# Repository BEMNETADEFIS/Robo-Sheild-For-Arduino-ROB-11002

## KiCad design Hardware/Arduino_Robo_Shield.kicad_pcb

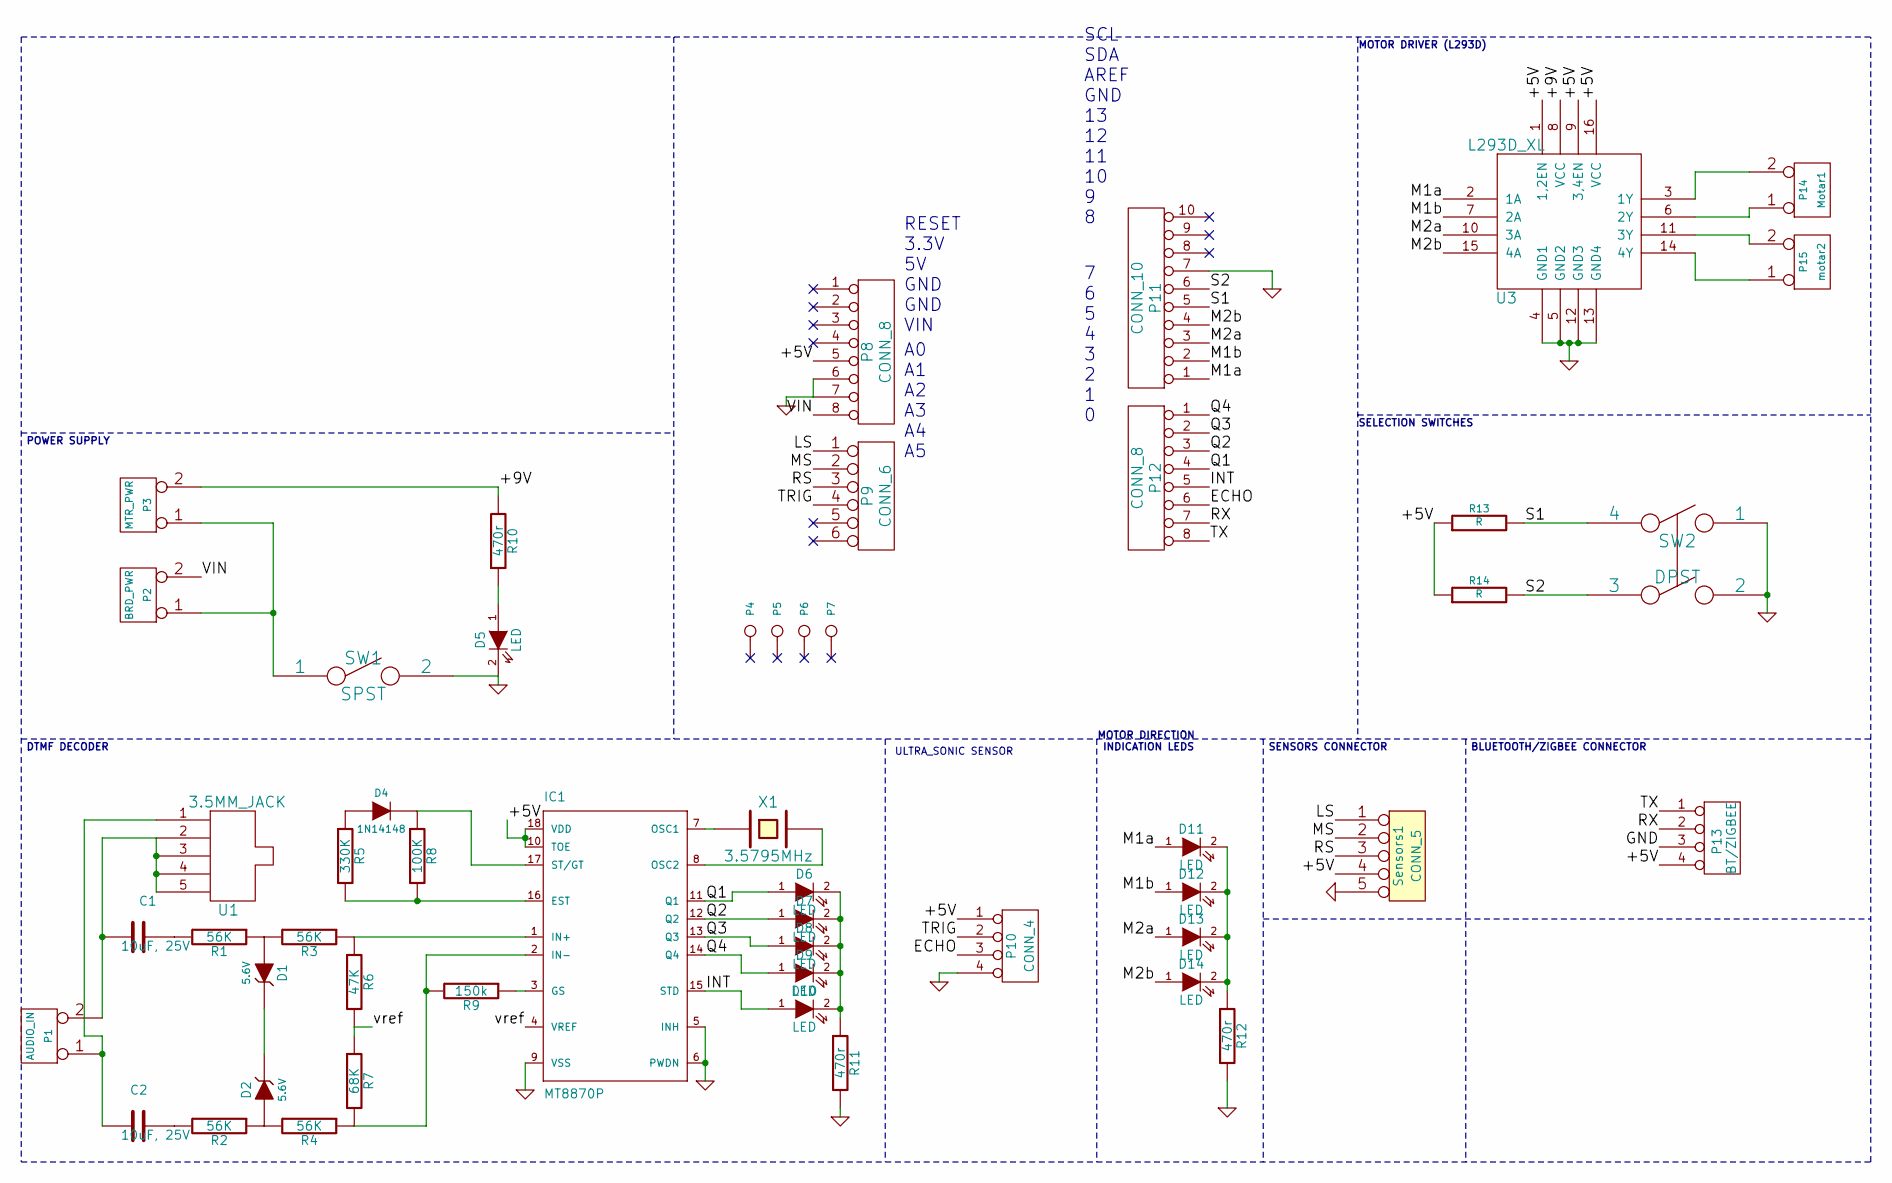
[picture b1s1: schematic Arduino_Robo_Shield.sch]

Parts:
C1, C2: 10uF, 25V
D1, D2: 5.6V
D4: 1N14148
D5, D6, D7, D8, D9, D10, D11, D12, D13, D14: LED
IC1: MT8870P; mitel-DIL18
P1: AUDIO_IN
P2: BRD_PWR
P3: MTR_PWR
P4, P5, P6, P7: CONN_1
P8, P12: CONN_8
P9: CONN_6
P10: CONN_4
P11: CONN_10
P13: BT/ZIGBEE
P14: Motar1
P15: motar2
R1, R2, R3, R4: 56K
R5: 330K
R6: 47K
R7: 68K
R8: 100K
R9: 150k
R10, R11, R12: 470r
R13, R14: R
SW1: SPST
SW2: DPST
Sensors1: CONN_5
U1: 3.5MM_JACK
U3: L293D_XL
X1: 3.5795MHz

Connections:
/+5V: IC1.10 (TOE), IC1.18 (VDD), P8.5, P10.1, P13.4, R13.1, R14.1, Sensors1.4, U3.1 (1,2EN), U3.9 (3,4EN), U3.16 (VCC)
/+9V: P3.2 (PM), R10.2, U3.8 (VCC)
/ECHO: P10.3, P12.6
/INT: D10.1 (A), IC1.15 (STD), P12.5
/LS: P9.1, Sensors1.1
/M1a: D11.1 (A), P11.1, U3.2 (1A)
/M1b: D12.1 (A), P11.2, U3.7 (2A)
/M2a: D13.1 (A), P11.3, U3.10 (3A)
/M2b: D14.1 (A), P11.4, U3.15 (4A)
/MS: P9.2, Sensors1.2
/Q1: D6.1 (A), IC1.11 (Q1), P12.4
/Q2: D7.1 (A), IC1.12 (Q2), P12.3
/Q3: D8.1 (A), IC1.13 (Q3), P12.2
/Q4: D9.1 (A), IC1.14 (Q4), P12.1
/RS: P9.3, Sensors1.3
/RX: P12.7, P13.2
/S1: P11.5, R13.2, SW2.4
/S2: P11.6, R14.2, SW2.3
/TRIG: P9.4, P10.2
/TX: P12.8, P13.1
/VIN: P2.2 (PM), P8.8
/vref: IC1.4 (VREF), R6.2, R7.1
GND: D5.2 (K), IC1.5 (INH), IC1.6 (PWDN), IC1.9 (VSS), P8.6, P8.7, P10.4, P11.7, P13.3, R11.2, R12.2, SW1.2, SW2.1, SW2.2, Sensors1.5, U3.4 (GND1), U3.5 (GND2), U3.12 (GND3), U3.13 (GND4)
unnamed: IC1.3 (GS), R9.1
unnamed: D1.2 (K), D2.2 (K)
unnamed: IC1.1 (IN+), R3.1, R6.1
unnamed: D4.2 (K), IC1.17 (ST/GT), R8.1
unnamed: IC1.7 (OSC1), X1.1
unnamed: IC1.8 (OSC2), X1.2
unnamed: P2.1, P3.1, SW1.1
unnamed: D5.1 (A), R10.1
unnamed: P15.1, U3.14 (4Y)
unnamed: P14.2 (PM), U3.3 (1Y)
unnamed: P15.2 (PM), U3.11 (3Y)
unnamed: P14.1, U3.6 (2Y)
unnamed: D2.1 (A), R2.1, R4.2
unnamed: D1.1 (A), R1.1, R3.2
unnamed: C2.2, P1.1, U1.1
unnamed: C2.1, R2.2
unnamed: C1.2, P1.2 (PM), U1.2, U1.3, U1.4, U1.5
unnamed: C1.1, R1.2
unnamed: D4.1 (A), R5.1
unnamed: IC1.16 (EST), R5.2, R8.2
unnamed: D6.2 (K), D7.2 (K), D8.2 (K), D9.2 (K), D10.2 (K), R11.1
unnamed: IC1.2 (IN-), R4.1, R7.2, R9.2
unnamed: D11.2 (K), D12.2 (K), D13.2 (K), D14.2 (K), R12.1

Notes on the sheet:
MOTOR DRIVER (L293D)
POWER SUPPLY
DTMF DECODER
MOTOR DIRECTION INDICATION LEDS
SENSORS CONNECTOR
BLUETOOTH/ZIGBEE CONNECTOR
SELECTION SWITCHES
7 6 5 4 3 2 1 0
SCL SDA AREF GND 13 12 11 10 9 8
A0 A1 A2 A3 A4 A5
RESET 3.3V 5V GND GND VIN
ULTRA_SONIC SENSOR

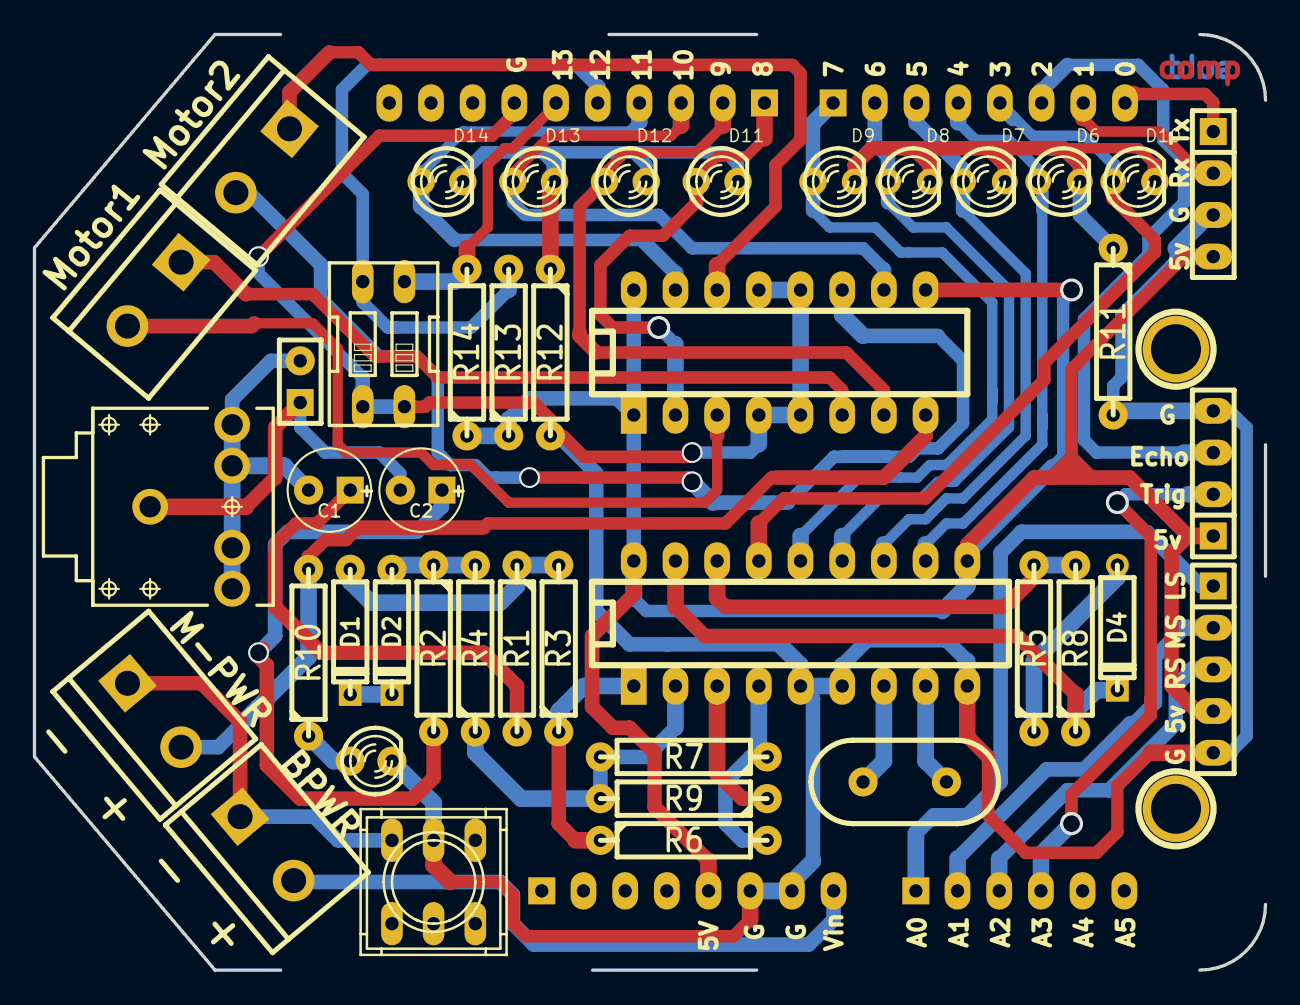
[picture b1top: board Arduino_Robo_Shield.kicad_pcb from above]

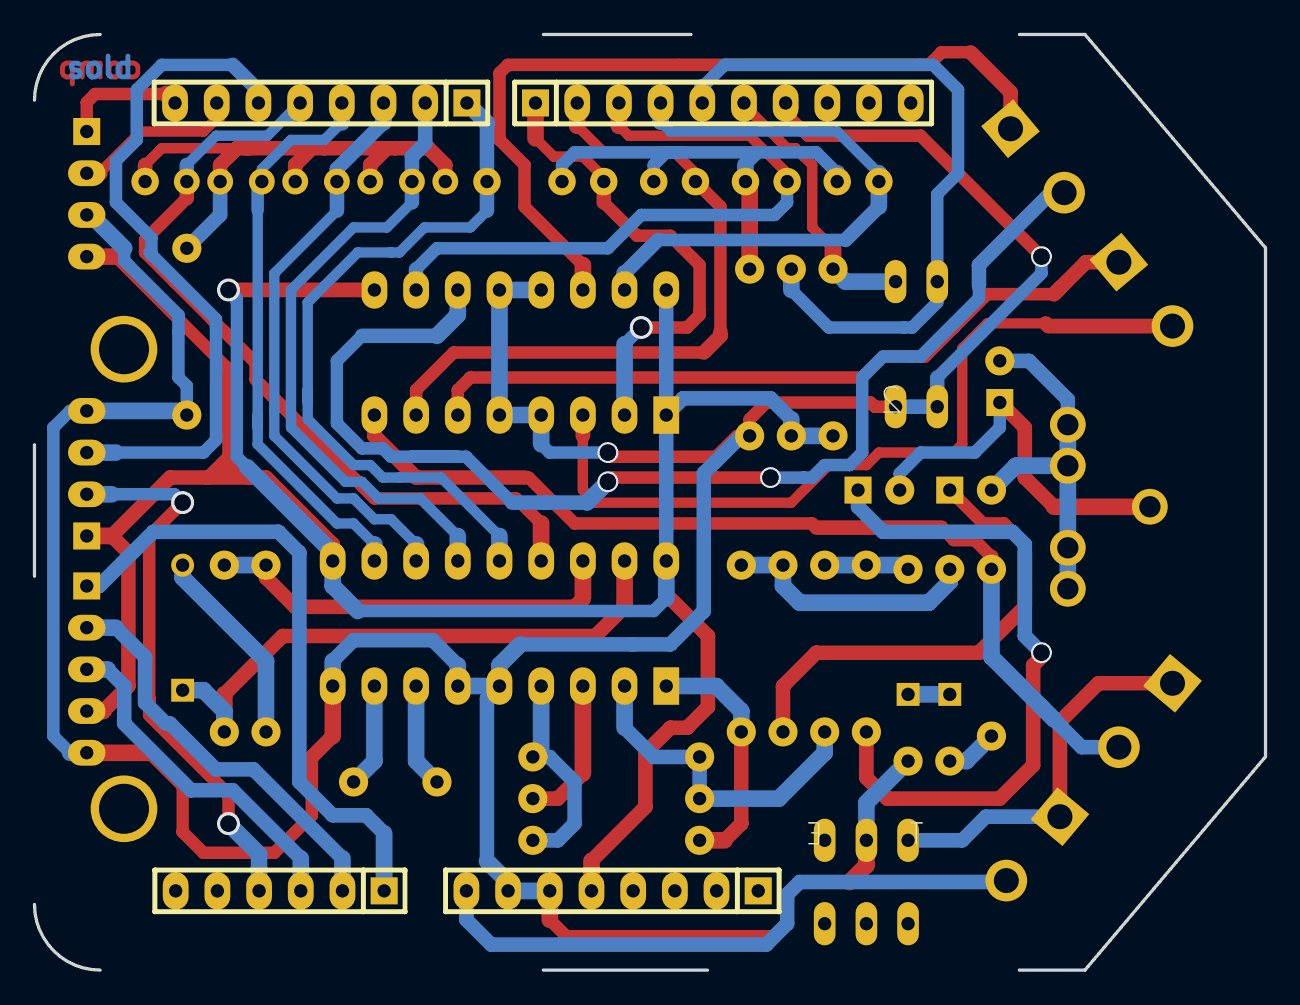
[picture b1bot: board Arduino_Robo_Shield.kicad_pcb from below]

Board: 2 copper layers, 75.0 x 57.0 mm, 49 parts (4 on the bottom side), 46 nets.

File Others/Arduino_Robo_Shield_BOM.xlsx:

Id | Designator | Package | Quantity | Designation | Supplier and ref
1 | SW1 | switch-misc-9077-2 | 1 | SPST
2 | U1 | SparkFun-AUDIO-JACK | 1 | 3.5MM_JACK
3 | P12,P8 | SIL-8 | 2 | CONN_8
4 | P9 | SIL-6 | 1 | CONN_6
5 | Sensors1 | SIL-5 | 1 | CONN_5
6 | P13 | SIL-4 | 1 | BT/ZIGBEE
7 | P10 | SIL-4 | 1 | CONN_4
8 | P1 | SIL-2 | 1 | AUDIO_IN
9 | P11 | SIL-10 | 1 | CONN_10
10 | R11,R10,R12 | R4 | 3 | 470r
11 | R9 | R4 | 1 | 150k
12 | R1,R4,R3,R2 | R4 | 4 | 56K
13 | R7 | R4 | 1 | 68K
14 | R6 | R4 | 1 | 47K
15 | R5 | R4 | 1 | 330K
16 | R8 | R4 | 1 | 100K
17 | D10,D9,D7,D5,D14,D6,D11,D13,D12,D8 | LED-3MM | 10 | LED
18 | X1 | HC-49V | 1 | 3.5795MHz
19 | IC1 | DIP-18__300_ELL | 1 | MT8870P
20 | U3 | DIP-16__300_ELL | 1 | L293D_XL
21 | D2,D1 | D3 | 2 | 5.6V
22 | D4 | D3 | 1 | 1N14148
23 | C2,C1 | C1V5 | 2 | 10uF, 25V
24 | P14 | bornier2 | 1 | Motar1
25 | P15 | bornier2 | 1 | motar2
26 | P3 | bornier2 | 1 | MTR_PWR
27 | P7,P5 | 1pin | 2 | CONN_1
28 | SW2 | SparkFun-DIPSWITCH-02 | 1 | DPST
29 | R13,R14 | R4 | 2 | R
30 | P2 | bornier2 | 1 | BRD_PWR

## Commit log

2015-05-21 created folders for test
    testing
2015-05-21 testing
2015-05-21 test
2015-05-21 hello world
2015-05-21 deleted
2015-05-21 Added design Files
2015-05-21 added folder structure
2015-05-21 added file
    text doc
2015-05-21 added files
2015-05-22 Beautified Schematic
    Changed the layout style of schematic, generated pdf with the plot
    option
2015-05-29 Obstacle Avoidance
    Added code for Obstacle Avoidance robot
2015-05-29 Updated Comments
